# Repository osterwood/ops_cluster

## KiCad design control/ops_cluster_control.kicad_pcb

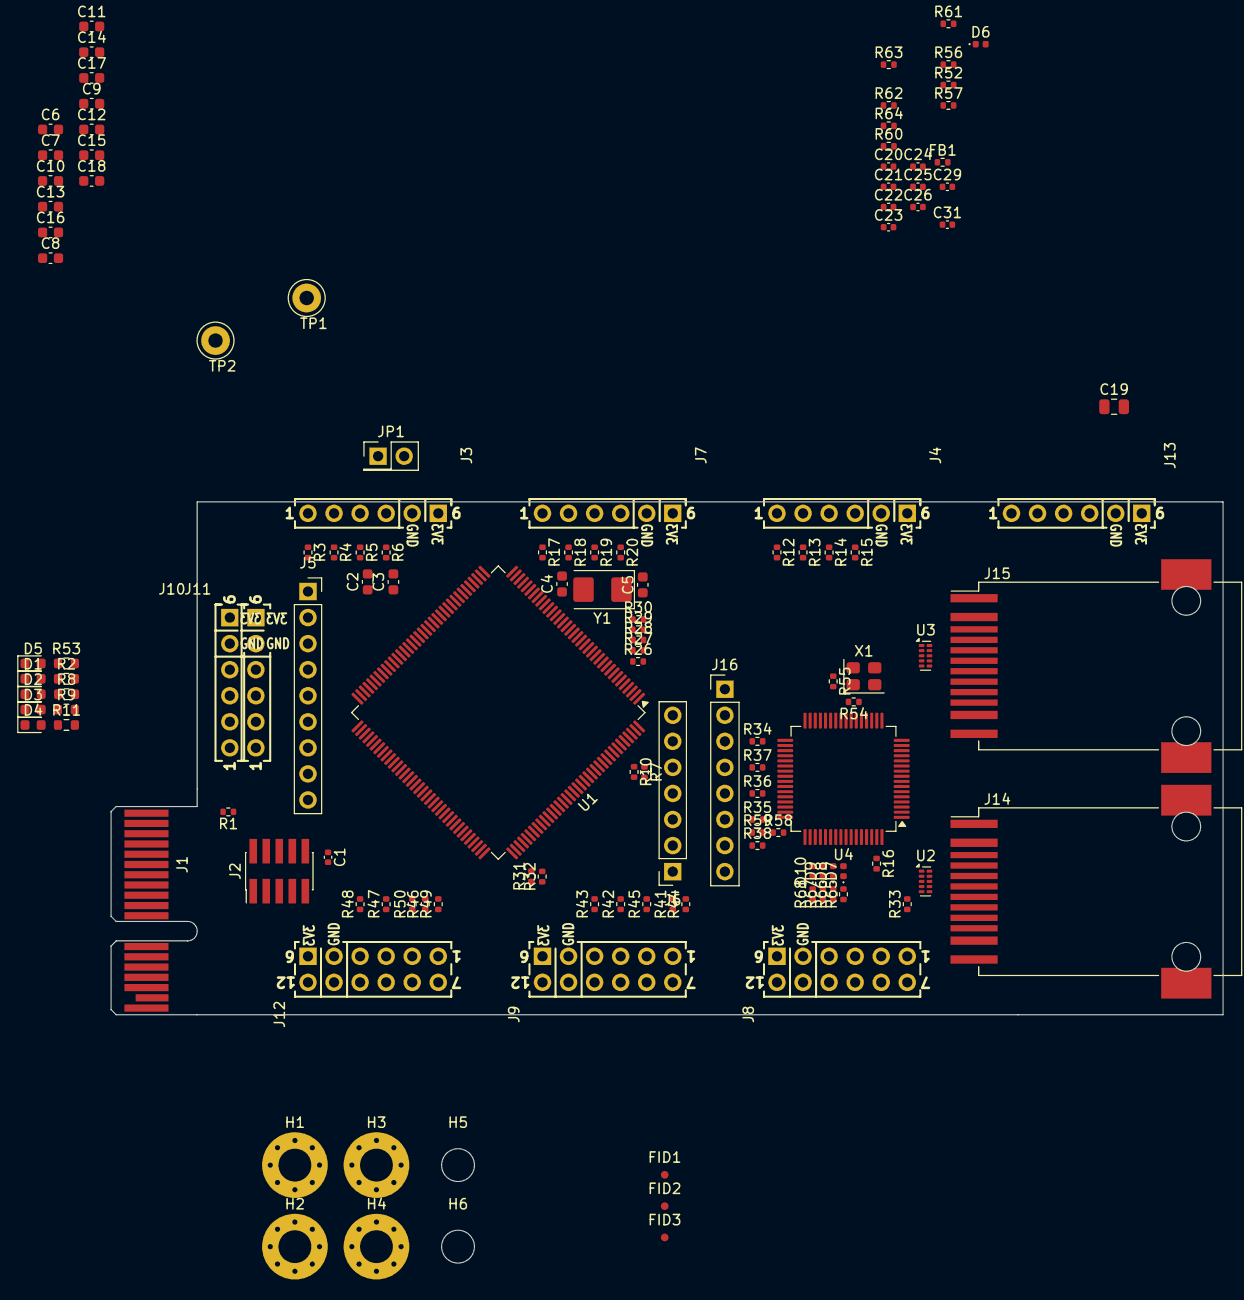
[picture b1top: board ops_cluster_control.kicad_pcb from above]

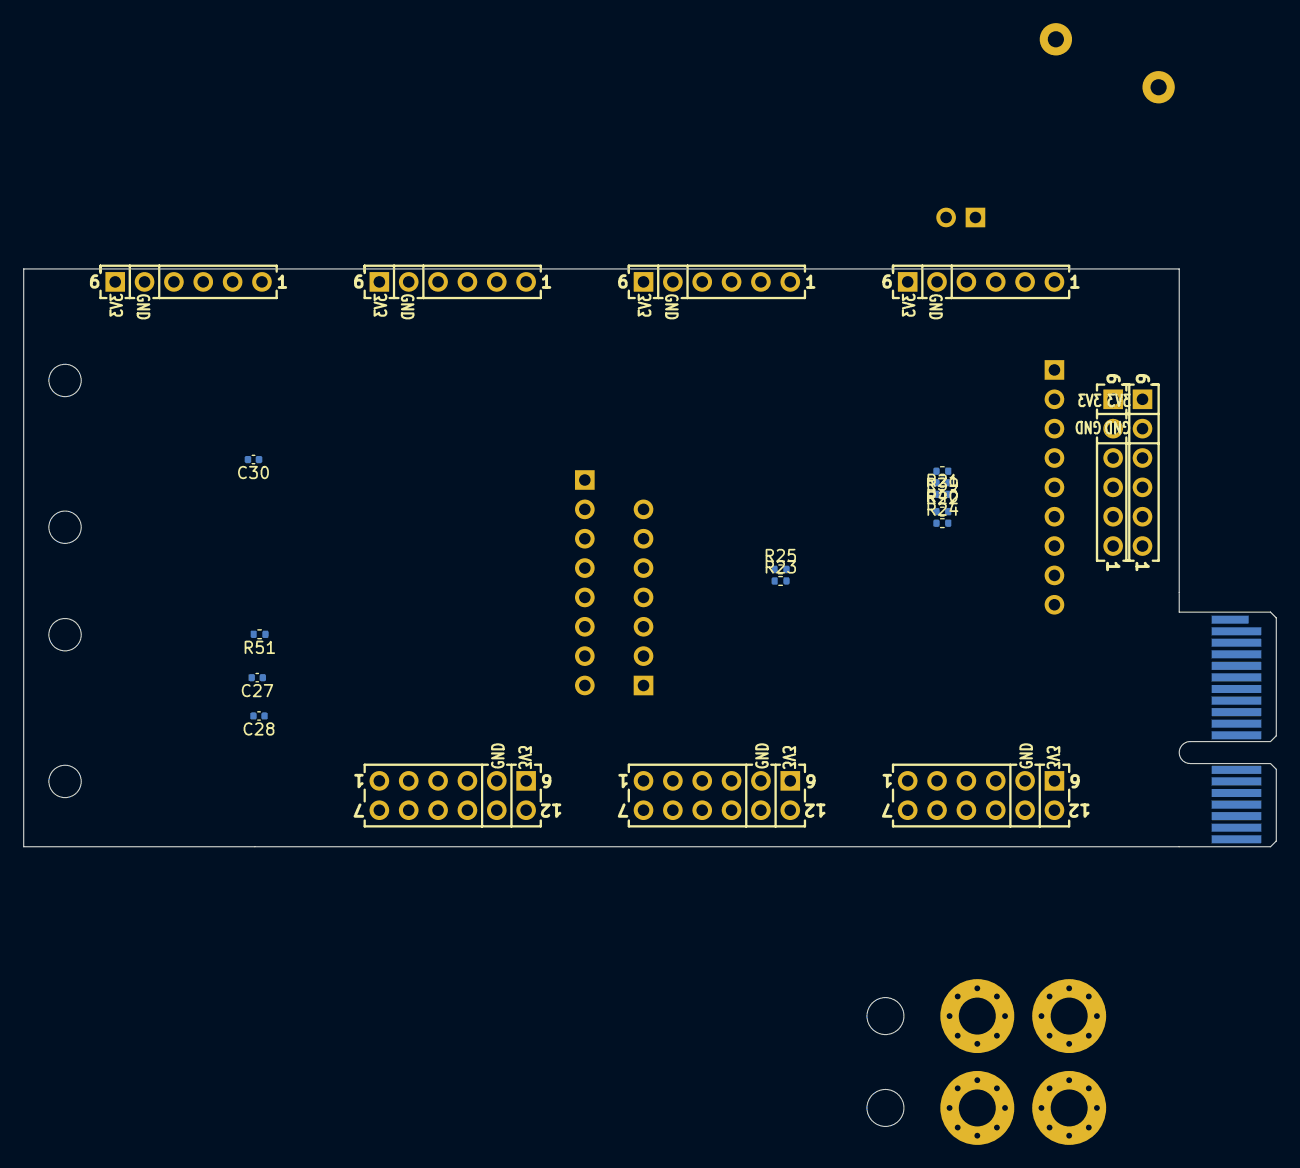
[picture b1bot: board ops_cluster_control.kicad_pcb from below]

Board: 2 copper layers, 108.4 x 50.0 mm, 144 parts (11 on the bottom side), 144 nets, no tracks yet.

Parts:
C1: 100n; C_0402_1005Metric
C2, C3: 2µ2 100mR; C_0603_1608Metric
C4, C5: 11p; C_0603_1608Metric
C6: 4µ7; C_0603_1608Metric
C7, C8, C9, C10, C11, C12, C13, C14, C15: 100n; C_0603_1608Metric
C16, C17, C18: 0µ1; C_0603_1608Metric
C19: 10 µF; C_0805_2012Metric
C20, C21, C22, C23, C24, C25, C26: 1 µF; C_0402_1005Metric
C27, C28, C29, C30: 0.1 µF; C_0402_1005Metric
C31: 4700 pF; C_0402_1005Metric
D1, D2, D3, D4, D5: LED; LED_0603_1608Metric
D6, D9: LED_GREEN; LED_0402_1005Metric
D7: LED_RED; LED_0402_1005Metric
D8: LED_ORANGE; LED_0402_1005Metric
D10: LED_BLUE; LED_0402_1005Metric
FB1: FerriteBead; R_0402_1005Metric
FID1, FID2, FID3: Fiducial; Fiducial_0.75mm_Mask1.5mm
H1, H2, H3, H4: MountingHole; MountingHole_3.2mm_M3_Pad_Via
H5, H6: MountingHole; MountingHole_3.2mm_M3
J1: MCU_card_interface; BUS_PCIexpress_x1
J2: SWD; PinHeader_2x05_P1.27mm_Vertical_SMD
J3, J4, J7, J10, J11, J13: Conn6x1; PMODPinSocket_1x06_P2.54mm_Horizontal
J5: Conn9x1; PinSocket_1x09_P2.54mm_Vertical
J6: Conn_01x07; PinSocket_1x07_P2.54mm_Vertical
J8, J9, J12: Conn6x2; PMODPinSocket_2x06_P2.54mm_Horizontal
J14, J15: Wuerth_74980111211; RJ45_Wuerth_74980111211_Horizontal
J16: Conn_01x08_Male; PinHeader_1x08_P2.54mm_Vertical
JP1: Conn2x1; PinHeader_2x01_P2.54mm_Vertical
R1, R3, R4, R7, R10, R12, R13, R16, R17, R18, R33, R34, R35, R36, R37, R38, R41, R42, R43, R44, R45, R46, R47, R48, R49, R50: 10k; R_0402_1005Metric
R2, R8, R9, R11, R53: 68; R_0603_1608Metric
R5, R6, R14, R15, R19, R20: 2K2; R_0402_1005Metric
R21, R22, R23, R24, R25, R26, R27, R28, R29, R30, R31, R32, R39, R40: 22; R_0402_1005Metric
R51, R52, R56, R57, R65, R66, R67, R68: 143Ω; R_0402_1005Metric
R54, R55: 10KΩ; R_0402_1005Metric
R58: 4K7; R_0402_1005Metric
R59: 0R; R_0402_1005Metric
R60: 6.49 KΩ; R_0402_1005Metric
R61: 1 MΩ; R_0402_1005Metric
R62: 10K; R_0402_1005Metric
R63: 143R; R_0402_1005Metric
R64: 4.7 KΩ; R_0402_1005Metric
TP1, TP2: TestPoint; TestPoint_Loop_D3.50mm_Drill1.4mm_Beaded
U1: STM32H753ZITx; LQFP-144_20x20mm_P0.5mm
U2, U3: TPD4S010DQAR; USON-10_2.5x1.0mm_P0.5mm
U4: KSZ8463FRLI; LQFP-64_10x10mm_P0.5mm
X1: ASE-25.000MHZ-LC; Oscillator_SMD_Abracon_ASE-4Pin_3.2x2.5mm
Y1: 8MHz; Crystal_SMD_5032-2Pin_5.0x3.2mm

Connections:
+3.3V: C19.2, C20.2, C21.2, C22.2, C23.2, J16.8, R51.2, R52.2, R54.1, R55.1, R56.2, R57.2, R58.2, R64.1, U4.9 (VDDA_3V3), U4.21 (VDD_IO), U4.30 (VDD_IO), U4.56 (VDD_IO), X1.4 (Vdd)
+3V3: C6.1, C7.1, C8.1, C9.1, C10.1, C11.1, C12.1, C13.1, C14.1, C15.1, C16.1, C17.1, C18.1, J2.1 (VTref), J3.6, J4.6, J5.1, J6.1, J7.6, J8.6, J8.12, J9.6, J9.12, J10.6, J11.6, J12.6, J12.12, J13.6, JP1.1 (A), R3.2, R4.2, R5.2, R6.2, R7.2, R12.2, R13.2, R14.2, R15.2, R16.2, R17.2, R18.2, R19.2, R20.2, R33.2, R34.2, R35.2, R36.2, R37.2, R38.2, R41.2, R42.2, R43.2, R44.2, R45.2, R46.2, R47.2, R48.2, R49.2, R50.2, R53.2, U1.6 (VBAT), U1.17 (VDD), U1.30 (VDD), U1.32 (VREF+), U1.33 (VDDA), U1.39 (VDD), U1.52 (VDD), U1.62 (VDD), U1.72 (VDD), U1.84 (VDD), U1.95 (VDD33_USB), U1.108 (VDD), U1.121 (VDD), U1.131 (VDD), U1.144 (VDD)
+5V: J1.B13 (5V), J1.B14 (5V)
/MCU/BOOT0: JP1.2 (B), R10.1, U1.138 (BOOT0)
/MCU/CRS_DV: U1.43 (PA7), U4.31 (RX_DV)
/MCU/I2C2.ALERT: J1.A9 (ALERT), J3.1, R3.1, U1.12 (PF2)
/MCU/I2C2.RESET: J1.A12 (RESET), J3.2, R4.1, U1.13 (PF3)
/MCU/I2C2.SCL: J1.A11 (SCL), J3.3, R5.1, U1.11 (PF1)
/MCU/I2C2.SDA: J1.A10 (SDA), J3.4, R6.1, U1.10 (PF0)
/MCU/I2C3.ALERT: J4.1, R12.1, U1.101 (PA9)
/MCU/I2C3.RESET: J4.2, R13.1, U1.102 (PA10)
/MCU/I2C3.SCL: J4.3, R14.1, U1.100 (PA8)
/MCU/I2C3.SDA: J4.4, R15.1, U1.99 (PC9)
/MCU/I2C4.ALERT: J7.1, R17.1, U1.53 (PF13)
/MCU/I2C4.RESET: J7.2, R18.1, U1.56 (PG0)
/MCU/I2C4.SCL: J7.3, R19.1, U1.54 (PF14)
/MCU/I2C4.SDA: J7.4, R20.1, U1.55 (PF15)
/MCU/LED0: R2.2, U1.87 (PG2)
/MCU/LED1: R8.2, U1.88 (PG3)
/MCU/LED2: R9.2, U1.89 (PG4)
/MCU/LED3: R11.2, U1.90 (PG5)
/MCU/OSC_IN: C4.1, U1.23 (PH0), Y1.2
/MCU/OSC_OUT: C5.1, U1.24 (PH1), Y1.1
/MCU/PB14: J5.2, U1.75 (PB14)
/MCU/PB15: J5.3, U1.76 (PB15)
/MCU/PD8: J5.4, U1.77 (PD8)
/MCU/PD9: J5.5, U1.78 (PD9)
/MCU/PD10: J5.6, U1.79 (PD10)
/MCU/PD11: J5.7, U1.80 (PD11)
/MCU/PD12: J5.8, U1.81 (PD12)
/MCU/PE2: J6.2, U1.1 (PE2)
/MCU/PE3: J6.3, U1.2 (PE3)
/MCU/PE4: J6.4, U1.3 (PE4)
/MCU/PE5: J6.5, U1.4 (PE5)
/MCU/PE6: J6.6, U1.5 (PE6)
/MCU/QSPI_CLK: J8.4, R30.2
/MCU/QSPI_IO0: J8.2, R28.2
/MCU/QSPI_IO1: J8.3, R29.2
/MCU/QSPI_IO2: J8.8, R27.2
/MCU/QSPI_IO3: J8.9, R26.2
/MCU/QSPI_XTRA7: J8.7, U1.14 (PF4)
/MCU/QSPI_XTRA10: J8.10, U1.15 (PF5)
/MCU/REF_CLK: U1.35 (PA1), U4.27 (REFCLK_I)
/MCU/RXD0: U1.44 (PC4), U4.35 (RXD0)
/MCU/RXD1: U1.45 (PC5), U4.34 (RXD1)
/MCU/SPI3.CIPO: J9.3, R42.1, U1.112 (PC11)
/MCU/SPI3.COPI: J9.2, R32.1
/MCU/SPI3.CS: J9.1, R41.1, U1.110 (PA15)
/MCU/SPI3.SCK: J9.4, R31.1, R43.1
/MCU/SPI3_INT: J9.7, R44.1, U1.114 (PD0)
/MCU/SPI3_RST: J9.8, R45.1, U1.115 (PD1)
/MCU/SPI4.CIPO: J16.5, R36.1, R40.2, U4.41 (SPI_DO)
/MCU/SPI4.COPI: J16.4, R37.1, U1.67 (PE14), U4.45 (SPI_DI/MDIO)
/MCU/SPI4.CS: J16.3, R34.1, U1.64 (PE11), U4.42 (SPI_CSN)
/MCU/SPI4.SCK: J16.6, R35.1, R39.2, U4.44 (SPI_SCLK/MDC)
/MCU/SPI6.CIPO: J1.A6 (CIPO), J12.3, R47.1, U1.127 (PG12)
/MCU/SPI6.COPI: J1.A5 (COPI), J12.2, R25.2
/MCU/SPI6.CS: J1.A8 (CS), J12.1, R46.1, U1.93 (PG8)
/MCU/SPI6.SCK: J1.A7 (SCK), J12.4, R23.2, R48.1
/MCU/SPI6_INT: J12.7, R49.1, U1.126 (PG11)
/MCU/SPI6_RST: J12.8, R50.1, U1.132 (PG15)
/MCU/SWCLK: J2.4 (SWDCLK/TCK), U1.109 (PA14)
/MCU/SWDIO: J2.2 (SWDIO/TMS), U1.105 (PA13)
/MCU/SWO: J2.6 (SWO/TDO), U1.133 (PB3)
/MCU/TXD0: R22.1, U4.26 (TXD0)
/MCU/TXD1: R24.1, U4.25 (TXD1)
/MCU/TXEN: R21.1, U4.22 (TX_EN)
/MCU/UART7_CTS: J13.1, U1.63 (PE10)
/MCU/UART7_RTS: J13.4, U1.60 (PE9)
/MCU/UART7_RX: J13.3, U1.58 (PE7)
/MCU/UART7_TX: J13.2, U1.59 (PE8)
/MCU/USART1_CTS: J10.1, U1.103 (PA11)
/MCU/USART1_RTS: J10.4, U1.104 (PA12)
/MCU/USART1_RX: J10.3, U1.137 (PB7)
/MCU/USART1_TX: J10.2, U1.136 (PB6)
/MCU/USART2_CTS: J11.1, U1.117 (PD3)
/MCU/USART2_RTS: J11.4, U1.118 (PD4)
/MCU/USART2_RX: J11.3, U1.122 (PD6)
/MCU/USART2_TX: J11.2, U1.119 (PD5)
/MCU/~ETH_INT: J16.7, R38.1, R59.1, U1.68 (PE15)
/MCU/~ETH_RST: D6.2 (A), J16.2, R16.1, R62.2, U1.69 (PB10), U4.63 (~RST)
/MCU/~QSPI_CS: J8.1, R33.1, U1.91 (PG6)
/MCU/~RST: C1.1, J2.10 (~RESET), U1.25 (NRST)
/NIC/P1LED0: J14.11, U4.60 (P1LED0)
/NIC/P1LED1: J14.2, U4.59 (P1LED1)
/NIC/P1V3: C24.2, FB1.1, U4.40 (VDD_L), U4.51 (VDD_L)
/NIC/P1V3_FILT: C25.2, C26.2, FB1.2, U4.6 (VDD_AL), U4.16 (VDD_COL)
/NIC/P2LED0: J15.11, U4.62 (P2LED0)
/NIC/P2LED1: J15.2, U4.61 (P2LED1)
/NIC/RX1_N: J14.8 (RD-), U2.5 (D2-), U2.6 (NC), U4.1 (RXM1)
/NIC/RX1_P: J14.6 (RD+), U2.4 (D2+), U2.7 (NC), U4.2 (RXP1)
/NIC/RX2_N: J15.8 (RD-), U3.5 (D2-), U3.6 (NC), U4.10 (RXM2)
/NIC/RX2_P: J15.6 (RD+), U3.4 (D2+), U3.7 (NC), U4.11 (RXP2)
/NIC/TX1_N: J14.5 (TD-), U2.2 (D1-), U2.9 (NC), U4.4 (TXM1)
/NIC/TX1_P: J14.3 (TD+), U2.1 (D1+), U2.10 (NC), U4.5 (TXP1)
/NIC/TX2_N: J15.5 (TD-), U3.2 (D1-), U3.9 (NC), U4.13 (TXM2)
/NIC/TX2_P: J15.3 (TD+), U3.1 (D1+), U3.10 (NC), U4.14 (TXP2)
Earth: C31.2, J14.10, J14.SH, J15.10, J15.SH, R61.2
GND: C1.2, C2.2, C3.2, C4.2, C5.2, C6.2, C7.2, C8.2, C9.2, C10.2, C11.2, C12.2, C13.2, C14.2, C15.2, C16.2, C17.2, C18.2, C19.1, C20.1, C21.1, C22.1, C23.1, C24.1, C25.1, C26.1, C27.2, C28.2, C29.2, C30.2, C31.1, D1.1 (K), D2.1 (K), D3.1 (K), D4.1 (K), D5.1 (K), H1.1, H2.1, H3.1, H4.1, J1.A1 (~EN), J1.B2 (GND), J1.B5 (GND), J1.B8 (GND), J1.B11 (GND), J1.B12 (GND), J1.B15 (GND), J1.B18 (GND), J2.3 (GND), J2.5 (GND), J2.9 (GNDDetect), J3.5, J4.5, J5.9, J6.7, J7.5, J8.5, J8.11, J9.5, J9.11, J10.5, J11.5, J12.5, J12.11, J13.5, J16.1, R1.1, R10.2, R60.1, R61.1, R62.1, R63.1, R65.1, R66.1, R67.1, R68.1, TP1.1, TP2.1, U1.16 (VSS), U1.31 (VSSA), U1.38 (VSS), U1.51 (VSS), U1.61 (VSS), U1.83 (VSS), U1.94 (VSS), U1.107 (VSS), U1.120 (VSS), U1.130 (VSS), U2.3 (GND), U2.8 (GND), U3.3 (GND), U3.8 (GND), U4.3 (AGND), U4.8 (AGND), U4.12 (AGND), U4.15 (FXSD2), U4.20 (DGND), U4.29 (DGND), U4.39 (DGND), U4.50 (DGND), U4.57 (DGND), U4.64 (FXSD1), X1.2 (GND)
unnamed: D1.2 (A), R2.1
unnamed: D2.2 (A), R8.1
unnamed: D3.2 (A), R9.1
unnamed: D4.2 (A), R11.1
unnamed: D5.2 (A), R53.1
unnamed: D6.1 (K), R63.2
unnamed: D7.2 (A), U4.55 (GPIO5)
unnamed: D7.1 (K), R65.2
unnamed: D8.2 (A), U4.54 (GPIO4)
unnamed: D8.1 (K), R66.2
unnamed: D9.2 (A), U4.53 (GPIO3)
unnamed: D9.1 (K), R67.2
unnamed: D10.2 (A), U4.52 (GPIO2)
unnamed: D10.1 (K), R68.2
unnamed: J1.B1 (SSEN), R1.2
unnamed: J14.1, R51.1
unnamed: J14.12, R52.1
unnamed: C28.1, J14.7 (RCT)
unnamed: C27.1, J14.4 (TCT)
unnamed: J15.1, R56.1
unnamed: J15.12, R57.1
unnamed: C30.1, J15.7 (RCT)
unnamed: C29.1, J15.4 (TCT)
unnamed: R21.2, U1.70 (PB11)
unnamed: R22.2, U1.73 (PB12)
unnamed: R24.2, U1.74 (PB13)
unnamed: R31.2, U1.111 (PC10)
unnamed: R32.2, U1.113 (PC12)
unnamed: R7.1, U1.143 (PDR_ON)
unnamed: R39.1, U1.65 (PE12)
unnamed: R40.1, U1.66 (PE13)
unnamed: R26.1, U1.18 (PF6)
unnamed: R27.1, U1.19 (PF7)
unnamed: R28.1, U1.20 (PF8)
unnamed: R29.1, U1.21 (PF9)
unnamed: R30.1, U1.22 (PF10)
unnamed: R23.1, U1.128 (PG13)
unnamed: R25.1, U1.129 (PG14)
unnamed: C2.1, C3.1, U1.71 (VCAP1), U1.106 (VCAP2)
unnamed: R54.2, U4.23 (EN_REFCLK_O)
unnamed: R60.2, U4.7 (ISET)
unnamed: U4.18 (X1), X1.3 (OUT)
unnamed: R58.1, R59.2, U4.43 (~INTR)
unnamed: R55.2, X1.1 (EN)
VIN: J1.B16 (VIN), J1.B17 (VIN)

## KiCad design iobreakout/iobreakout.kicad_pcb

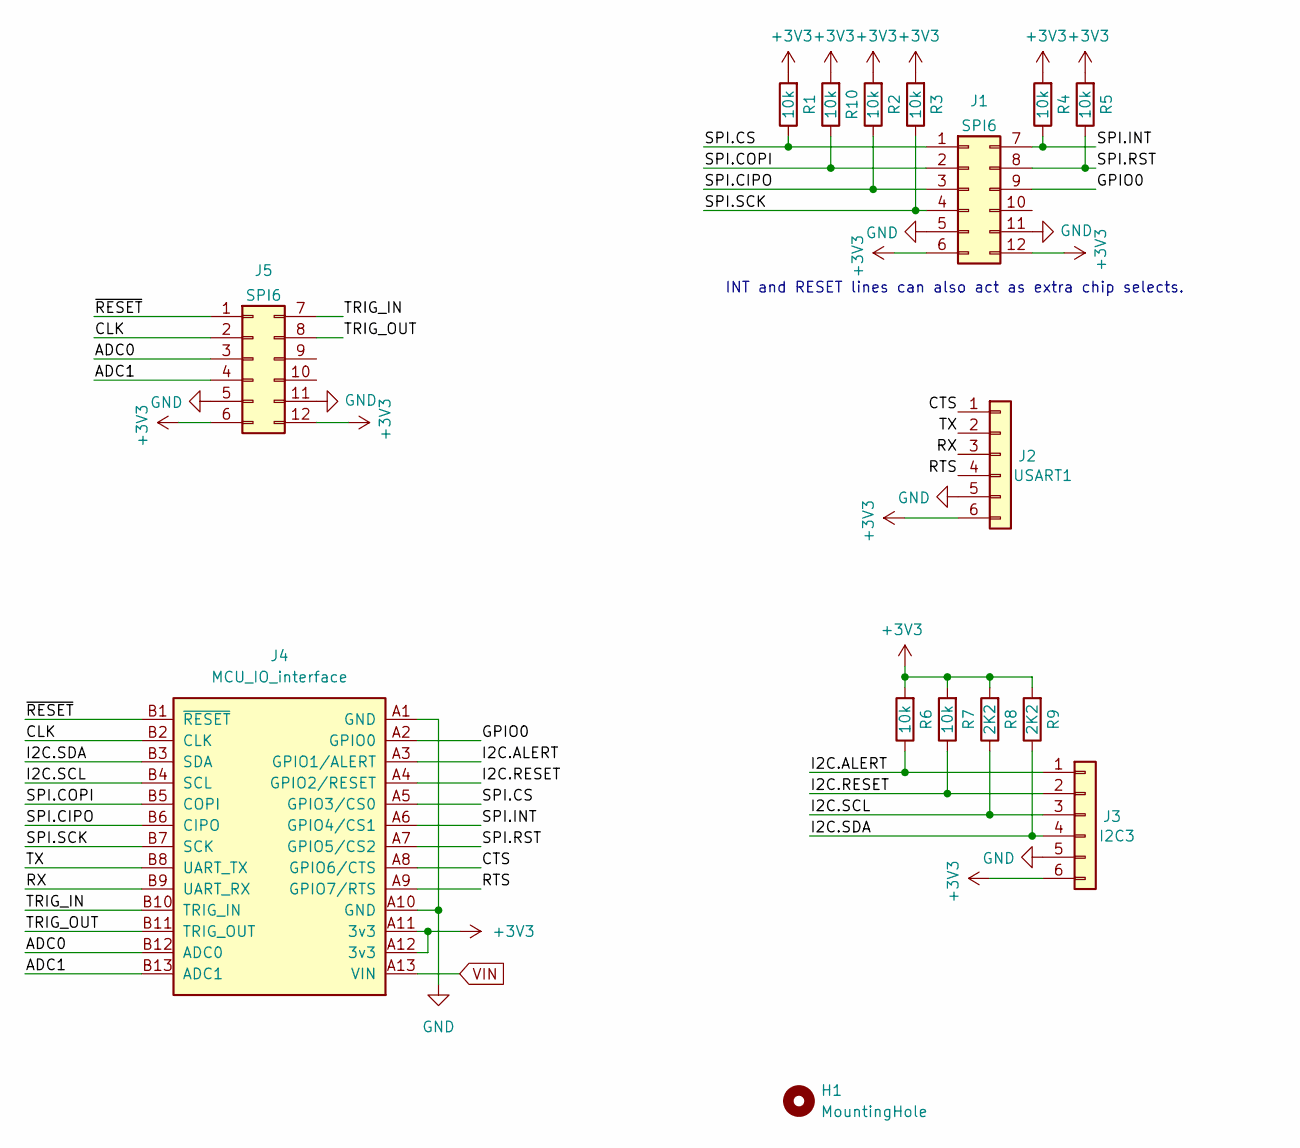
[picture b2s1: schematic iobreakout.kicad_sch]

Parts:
H1: MountingHole; MountingHole_2.7mm_M2.5
J1: Conn6x2; PMODPinSocket_2x06_P2.54mm_Horizontal; MPN PPTC062LJBN-RC
J2, J3: Conn6x1; PMODPinSocket_1x06_P2.54mm_Vertical; MPN FR20206HBNN
J4: MCU_IO_interface; M55-6002642R
J5: Conn6x2; PMODPinSocket_2x06_P2.54mm_Vertical; MPN PPTC062LJBN-RC
R1, R2, R3, R4, R5, R10: 10k; R_0603_1608Metric; MPN CR0603-JW-103ELF
R6, R7: 10k; R_0603_1608Metric
R8, R9: 2K2; R_0603_1608Metric

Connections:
+3V3: J1.6, J1.12, J2.6, J3.6, J4.A11 (3v3), J4.A12 (3v3), J5.6, J5.12, R1.2, R2.2, R3.2, R4.2, R5.2, R6.2, R7.2, R8.2, R9.2, R10.2
/ADC0: J4.B12 (ADC0), J5.3
/ADC1: J4.B13 (ADC1), J5.4
/CLK: J4.B2 (CLK), J5.2
/CTS: J2.1, J4.A8 (GPIO6/CTS)
/GPIO0: J1.9, J4.A2 (GPIO0)
/I2C.ALERT: J3.1, J4.A3 (GPIO1/ALERT), R6.1
/I2C.RESET: J3.2, J4.A4 (GPIO2/RESET), R7.1
/I2C.SCL: J3.3, J4.B4 (SCL), R8.1
/I2C.SDA: J3.4, J4.B3 (SDA), R9.1
/RTS: J2.4, J4.A9 (GPIO7/RTS)
/RX: J2.3, J4.B9 (UART_RX)
/SPI.CIPO: J1.3, J4.B6 (CIPO), R2.1
/SPI.COPI: J1.2, J4.B5 (COPI), R10.1
/SPI.CS: J1.1, J4.A5 (GPIO3/CS0), R1.1
/SPI.INT: J1.7, J4.A6 (GPIO4/CS1), R4.1
/SPI.RST: J1.8, J4.A7 (GPIO5/CS2), R5.1
/SPI.SCK: J1.4, J4.B7 (SCK), R3.1
/TRIG_IN: J4.B10 (TRIG_IN), J5.7
/TRIG_OUT: J4.B11 (TRIG_OUT), J5.8
/TX: J2.2, J4.B8 (UART_TX)
/~RESET: J4.B1 (~RESET), J5.1
GND: J1.5, J1.11, J2.5, J3.5, J4.A1 (GND), J4.A10 (GND), J5.5, J5.11
VIN: J4.A13 (VIN)

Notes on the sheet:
INT and RESET lines can also act as extra chip selects.

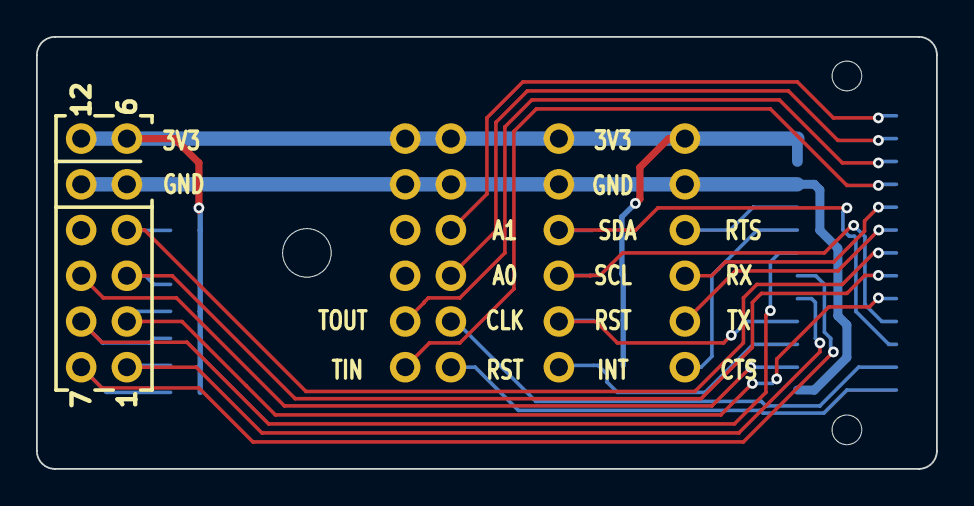
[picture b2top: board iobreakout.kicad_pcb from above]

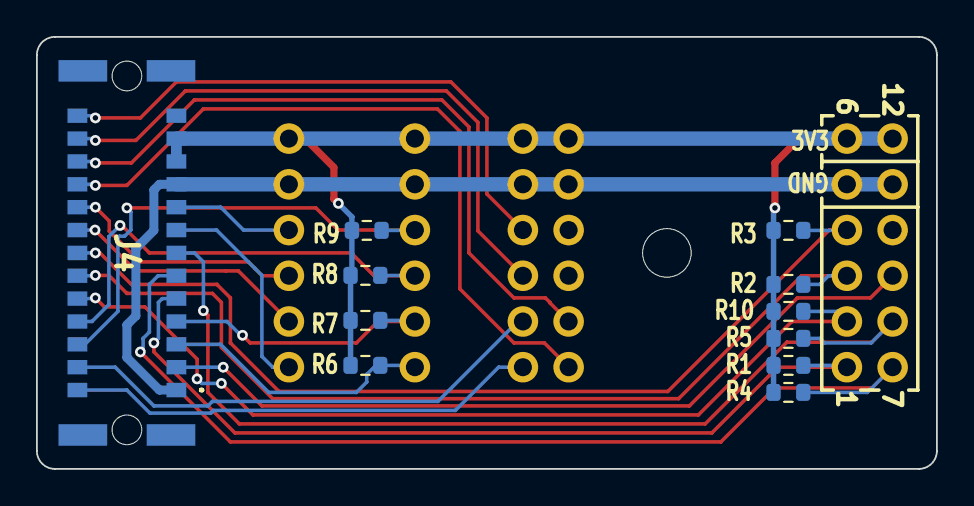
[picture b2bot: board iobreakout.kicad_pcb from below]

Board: 2 copper layers, 50.0 x 24.0 mm, 16 parts (11 on the bottom side), 23 nets.

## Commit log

2025-12-11 Simple IO breakout for main MCU PCB
2025-12-11 Add libraries
2025-12-11 In progress MCU PCB
